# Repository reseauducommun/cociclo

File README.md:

# cociclo
An airborne particles, Carbon Monoxyde (CO), temperature and humidity sensor circuit based on the ESP8266 (Wemos).  One version sends data to mysql and allows for the exploration of visualisations.  The other turns the pollution levels into sound for a participatory walk. 

For more information about the art and activism project : https://artengine.ca/acastonguay

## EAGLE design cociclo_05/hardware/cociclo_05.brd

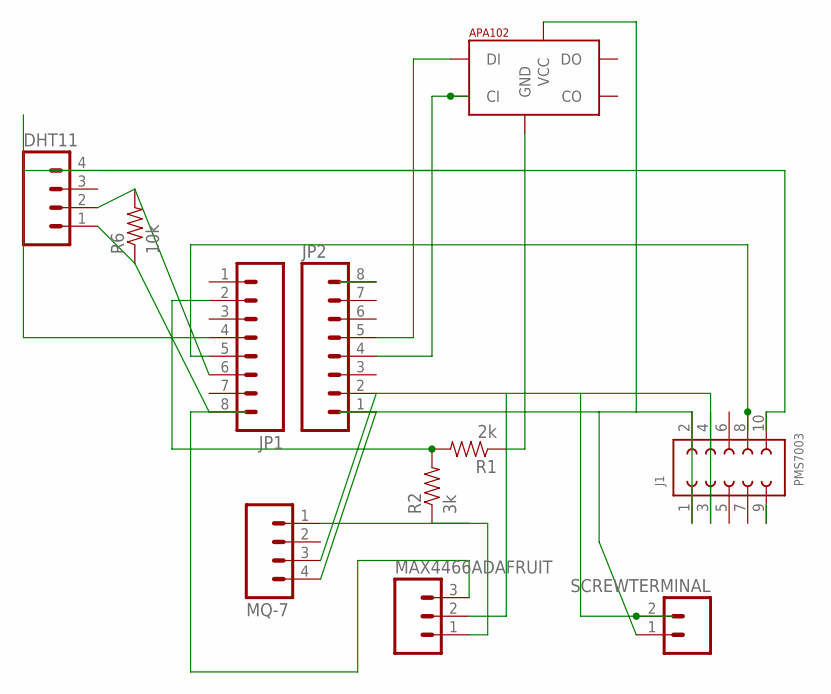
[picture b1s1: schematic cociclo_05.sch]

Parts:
DHT11: M04PTH; 1X04
J1: PMS7003; 621X1021021
JP1, JP2: M08; 1X08_ROUND
MAX4466ADAFRUIT: M03PTH; 1X03
MQ-7: M04PTH; 1X04
R1: 2k; 1206
R2: 3k; 1206
R6: 10k; 1206
SCREWTERMINAL: M023.5MM; SCREWTERMINAL-3.5MM-2
SK9822LED: APA1025050; APA102_5050

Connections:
7RX: J1.8 (7), JP1.5
9TX: J1.10 (6), JP1.4
10SET: J1.9 (5)
+5V: J1.1, J1.2 (10), JP2.1, MQ-7.4, SCREWTERMINAL.1, SK9822LED.1 (VCC)
ADC: JP1.2, R1.2, R2.2
CH_PD: DHT11.1, JP1.8, MAX4466ADAFRUIT.3, R6.1
D2: JP2.5, SK9822LED.4 (DI)
GND: DHT11.4, J1.3 (2), J1.4 (9), JP2.2, MAX4466ADAFRUIT.2, MQ-7.3, R1.1, SCREWTERMINAL.2, SK9822LED.6 (GND)
GPIO14: DHT11.2, JP1.6, R6.2
MQ7ANALOG: MAX4466ADAFRUIT.1, MQ-7.1, R2.1
unnamed: JP2.4, SK9822LED.5 (CI)

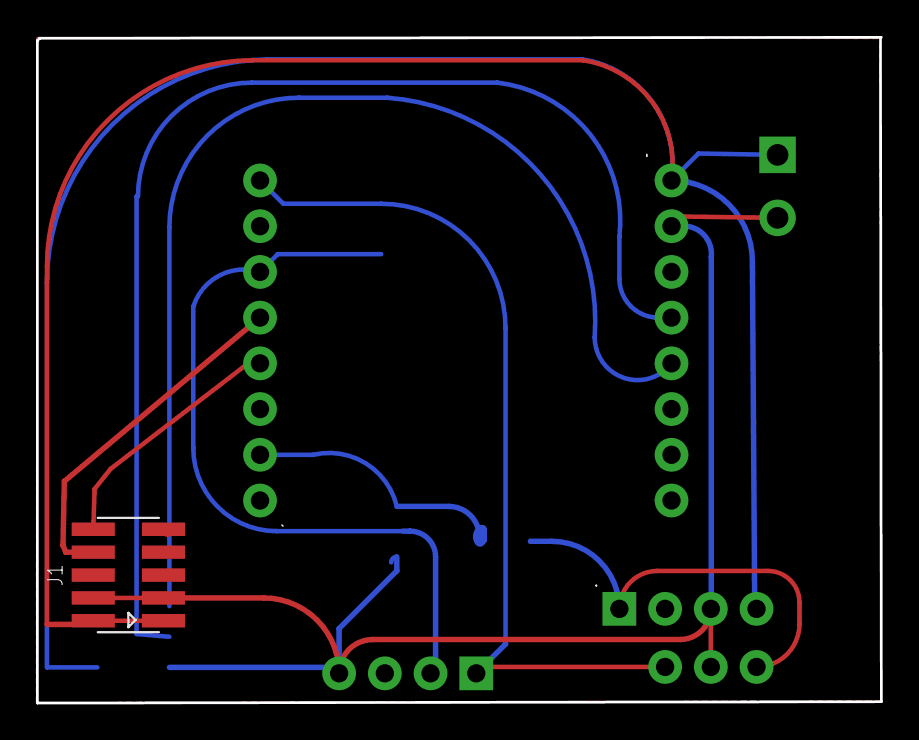
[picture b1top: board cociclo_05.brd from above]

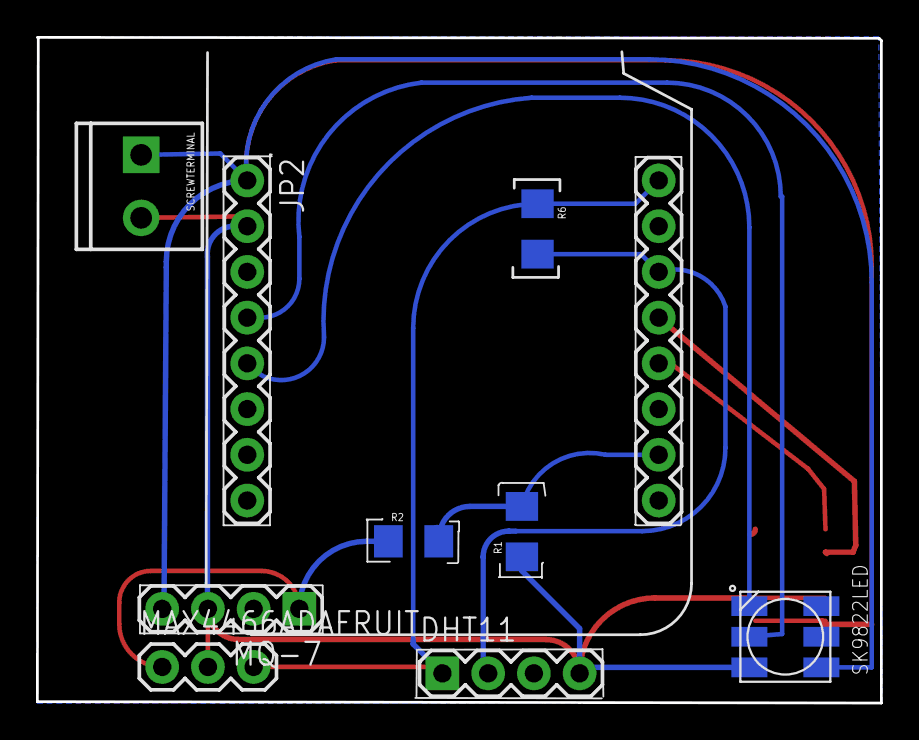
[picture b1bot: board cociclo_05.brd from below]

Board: 2 copper layers, 46.9 x 37.0 mm, 11 parts (10 on the bottom side), 10 nets.

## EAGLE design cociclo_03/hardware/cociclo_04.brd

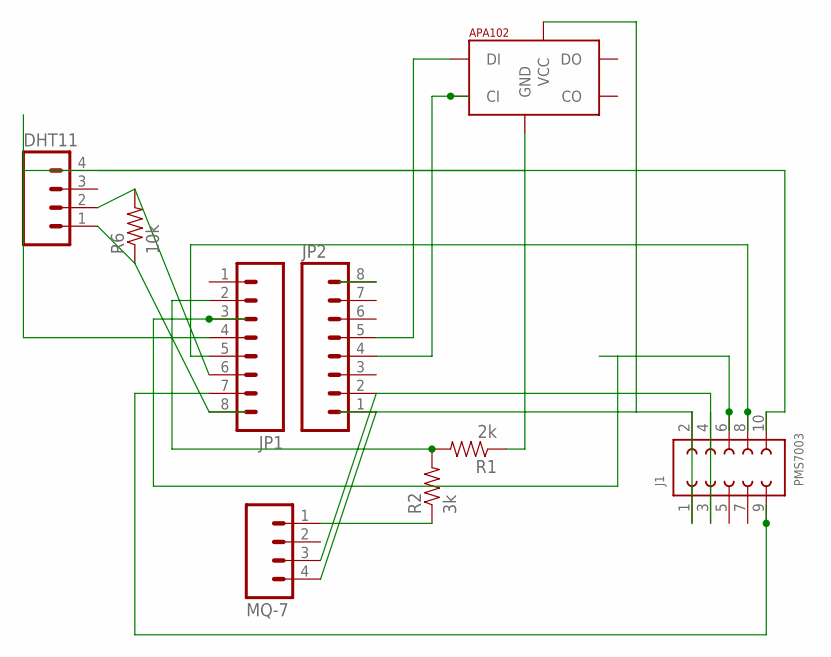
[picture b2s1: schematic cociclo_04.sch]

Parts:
DHT11: M04PTH; 1X04
J1: PMS7003; 621X1021021
JP1, JP2: M08; 1X08_ROUND
LED: APA1025050; APA102_5050
MQ-7: M04PTH; 1X04
R1: 2k; 1206
R2: 3k; 1206
R6: 10k; 1206

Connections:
5RESET: J1.6 (8), JP1.3
7RX: J1.8 (7), JP1.5
9TX: J1.10 (6), JP1.4
10SET: J1.9 (5), JP1.7
+5V: J1.1, J1.2 (10), JP2.1, LED.1 (VCC), MQ-7.4
ADC: JP1.2, R1.2, R2.2
CH_PD: DHT11.1, JP1.8, R6.1
D2: JP2.5, LED.4 (DI)
GND: DHT11.4, J1.3 (2), J1.4 (9), JP2.2, LED.6 (GND), MQ-7.3, R1.1
GPIO14: DHT11.2, JP1.6, R6.2
MQ7ANALOG: MQ-7.1, R2.1
unnamed: JP2.4, LED.5 (CI)

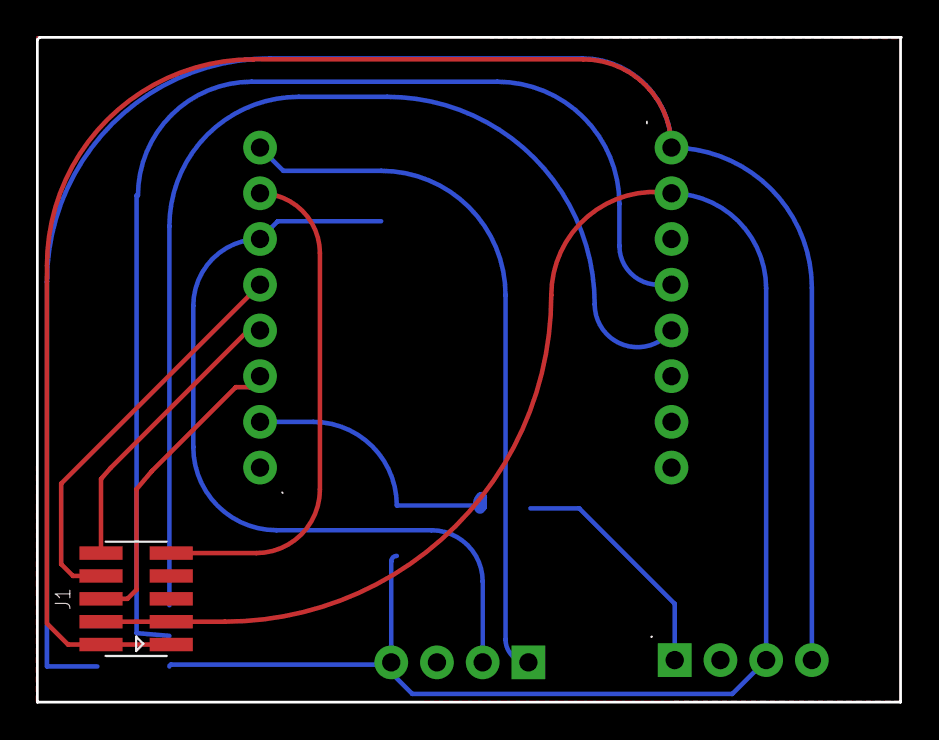
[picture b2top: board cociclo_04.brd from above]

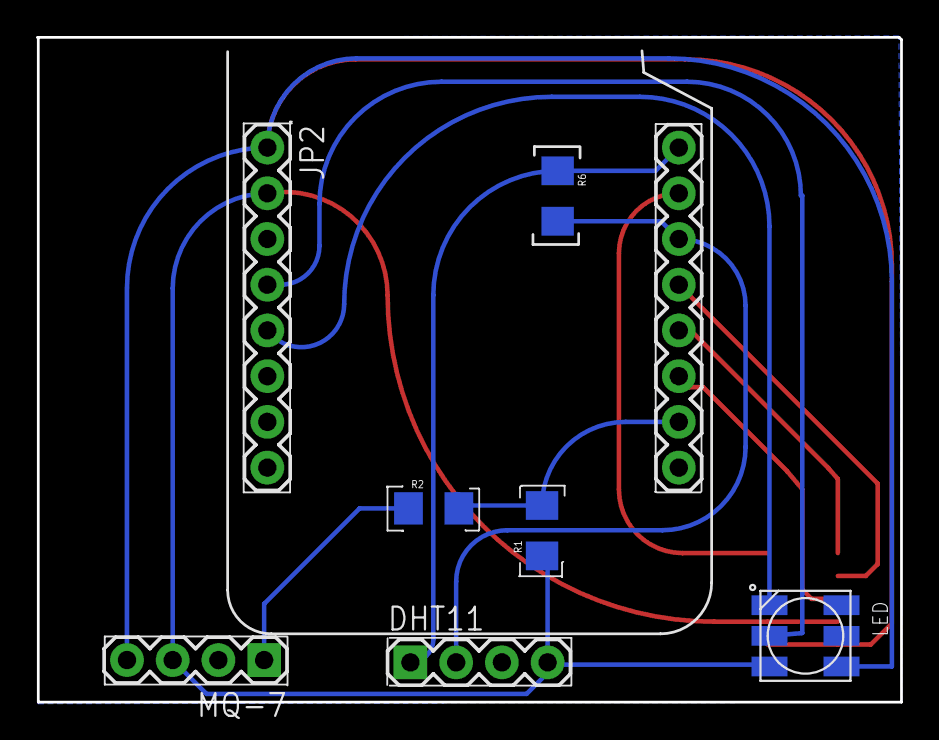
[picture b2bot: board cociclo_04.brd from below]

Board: 2 copper layers, 48.0 x 36.9 mm, 9 parts (8 on the bottom side), 12 nets.

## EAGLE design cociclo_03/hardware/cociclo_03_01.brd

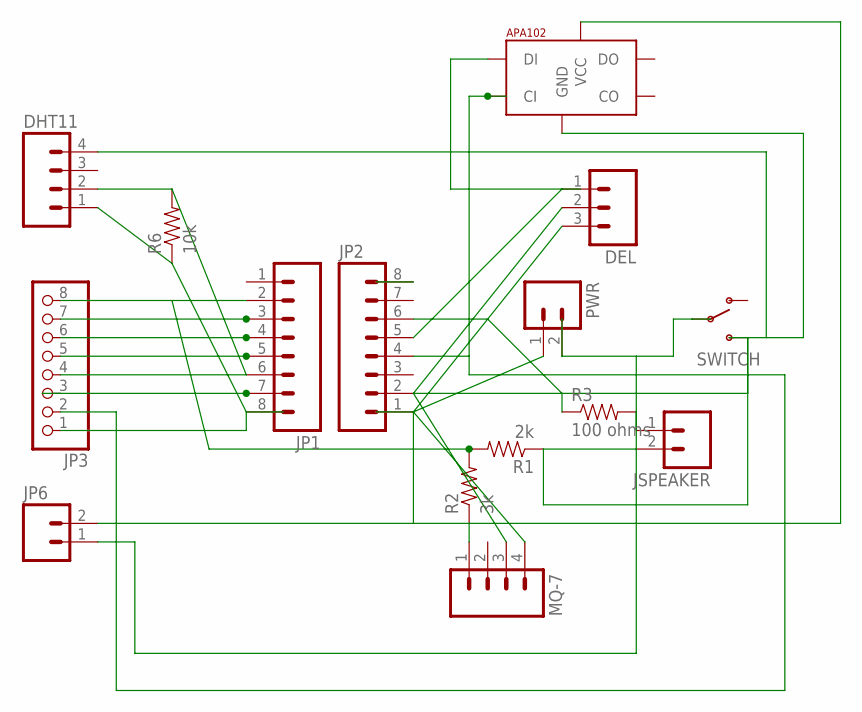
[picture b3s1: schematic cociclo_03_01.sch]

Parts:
DEL: M03PTH; 1X03
DHT11: M04PTH; 1X04
JP1, JP2: M08; 1X08_ROUND
JP3: PINHD-1X8-3.5MM; 1X08-3.5MM
JP6: M023.5MM; SCREWTERMINAL-3.5MM-2
JSPEAKER: M02PTH; 1X02
LED: APA1025050; APA102_5050
MQ-7: M04PTH; 1X04
PWR: M02LOCK_LONGPADS; 1X02_LOCK_LONGPADS
R1: 2k; 1206
R2: 3k; 1206
R3: 100 ohms; 1206
R6: 10k; 1206
SWITCH: SWITCH-SPDTKIT; SWITCH-SPDT_KIT

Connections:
+5V: DEL.3, JP2.1, JP6.2, LED.1 (VCC), MQ-7.4, PWR.1
ADC: JP1.2, JP3.8, R1.2, R2.2
CH_PD: DHT11.1, JP1.8, JP3.1, R6.1
D2: DEL.1, JP2.5, LED.4 (DI)
GND: DEL.2, DHT11.4, JP2.2, JSPEAKER.2, LED.6 (GND), MQ-7.3, R1.1, SWITCH.3 (S)
GPIO12: JP2.6, R3.1
GPIO14: DHT11.2, JP1.6, JP3.4, R6.2
MQ7ANALOG: MQ-7.1, R2.1
unnamed: JSPEAKER.1, R3.2
unnamed: JP1.7, JP3.3
unnamed: JP6.1, PWR.2, SWITCH.2
unnamed: JP2.4, JP3.2, LED.5 (CI)
unnamed: JP1.5, JP3.5
unnamed: JP1.4, JP3.6
unnamed: JP1.3, JP3.7

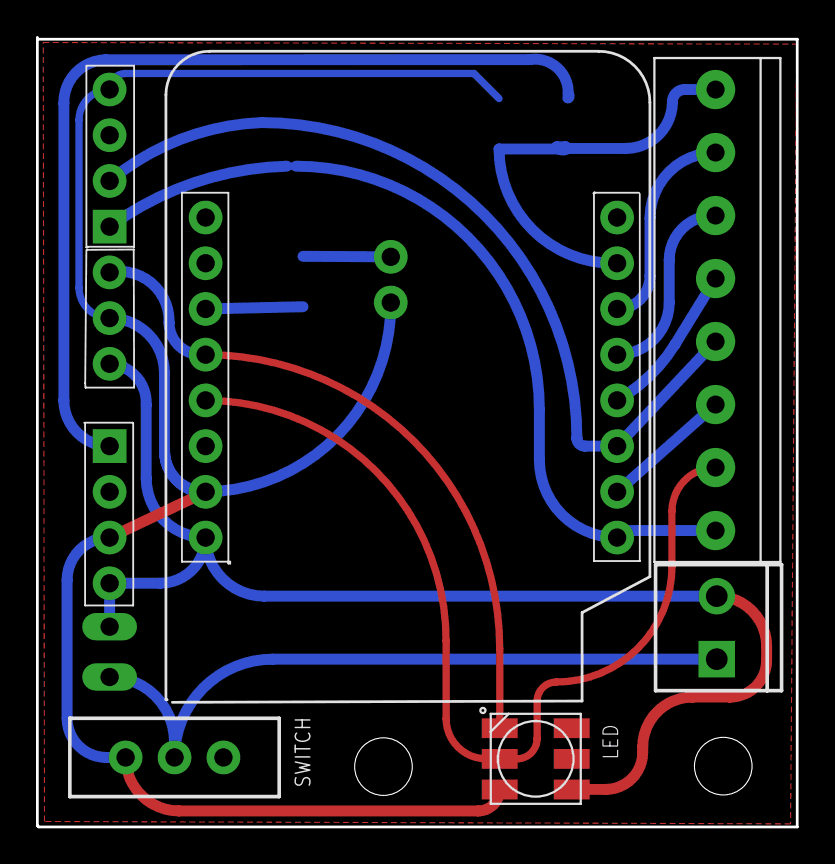
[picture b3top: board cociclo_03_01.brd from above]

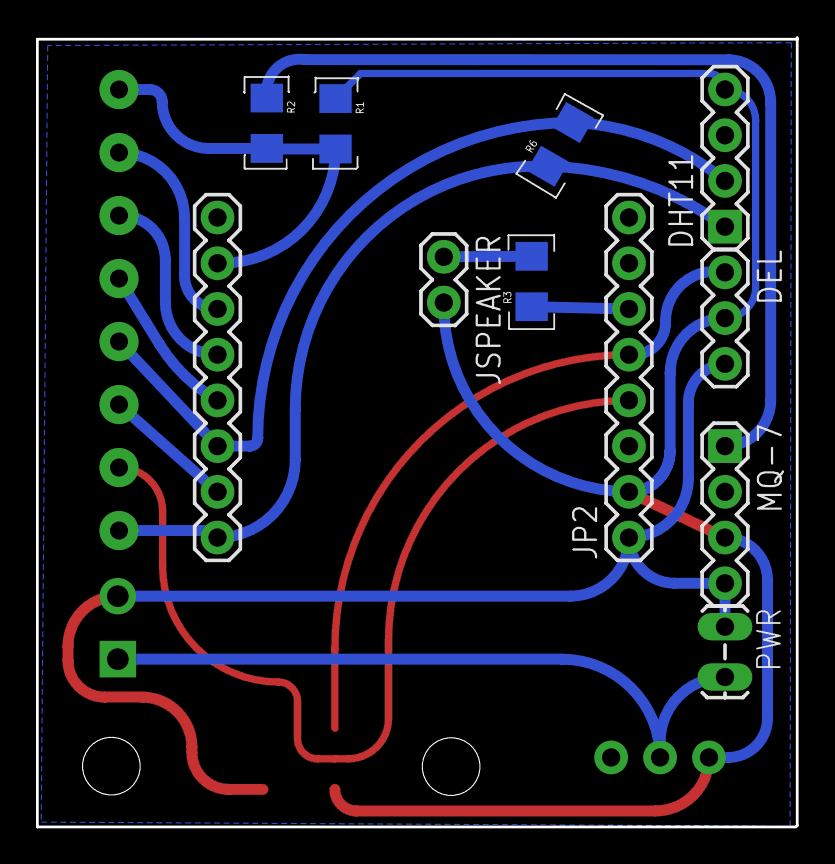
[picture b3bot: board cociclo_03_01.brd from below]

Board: 2 copper layers, 42.2 x 43.9 mm, 15 parts (11 on the bottom side), 15 nets.

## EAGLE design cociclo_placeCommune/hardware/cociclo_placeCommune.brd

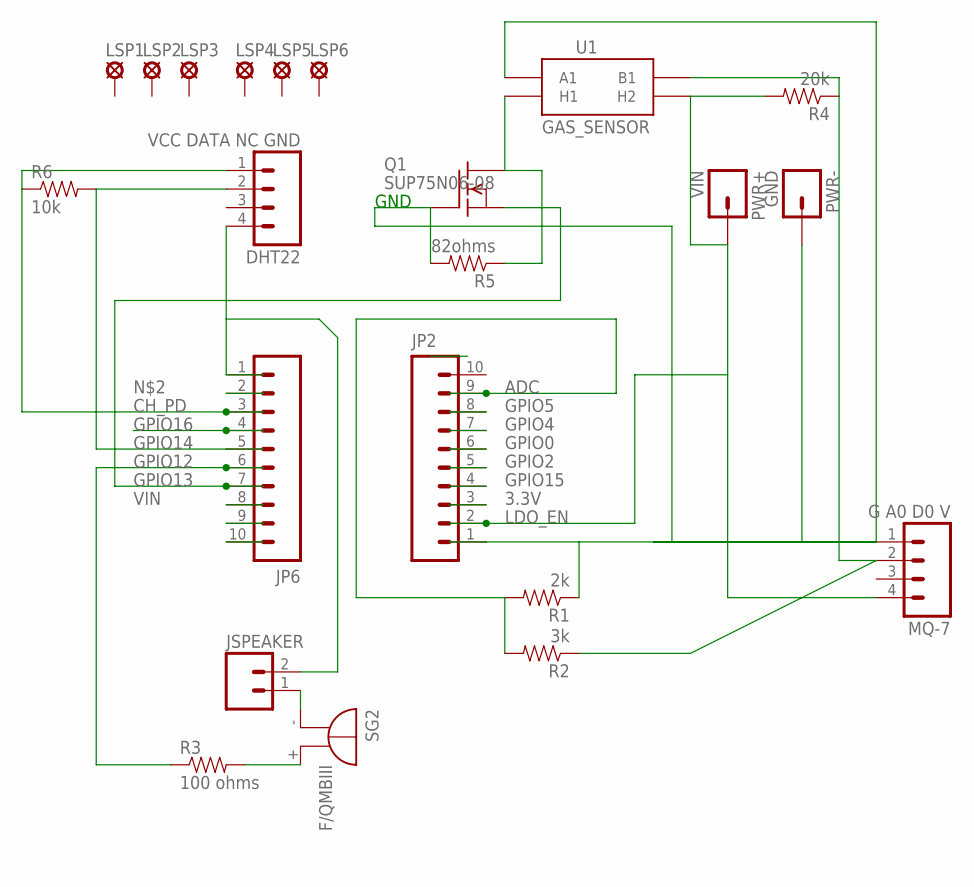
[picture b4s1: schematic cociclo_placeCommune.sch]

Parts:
DHT22: VCC DATA NC GND; 1X04
JP2, JP6: M10SILK_FEMALE_PTH; 1X10
JSPEAKER: M02PTH; 1X02
LSP1, LSP2, LSP3, LSP4, LSP5, LSP6: LSP10
MQ-7: G A0 D0 V; 1X04
PWR+: VIN; 1X01NS-KIT
PWR-: GND; 1X01NS-KIT
Q1: SUP75N06-08; TO220
R1: 2k; 1206
R2: 3k; 1206
R3: 100 ohms; 1206
R4: 20k; 1206
R5: 82ohms; 1206
R6: 10k; 1206
SG2: F/QMBIII
U1: GAS_SENSOR; MQ-3

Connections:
3.3V: JP2.3
ADC: JP2.9, R1.2, R2.2
CH_PD: DHT22.1, JP6.3, R6.1
GND: JP2.1, JP6.10, MQ-7.1, PWR-.1, Q1.1 (G), R1.1, R5.2, U1.A1
GPIO0: JP2.6
GPIO2: JP2.5
GPIO4: JP2.7
GPIO5: JP2.8
GPIO12: JP6.6, R3.1
GPIO13: JP6.7, Q1.3 (S)
GPIO14: DHT22.2, JP6.5, R6.2
GPIO15: JP2.4
GPIO16: JP6.4
LDO_EN: JP2.2, MQ-7.4, PWR+.1, R4.2, U1.HB (H2)
unnamed: MQ-7.2, R2.1, R4.1, U1.B1
unnamed: R3.2, SG2.+ (-)
unnamed: JSPEAKER.1, SG2.- (+)
unnamed: Q1.2 (D), R5.1, U1.HA (H1)
RESET_5V: DHT22.4, JP6.1, JSPEAKER.2
VBAT: JP6.9
VIN: JP6.8

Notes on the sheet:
GND

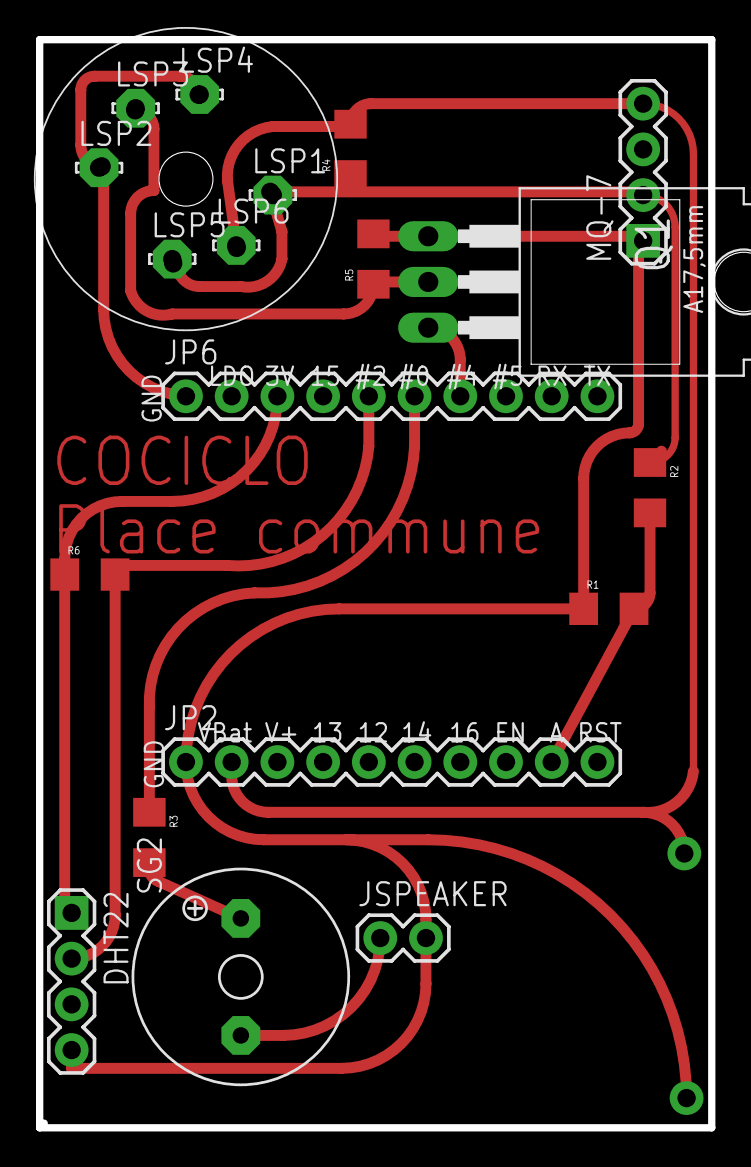
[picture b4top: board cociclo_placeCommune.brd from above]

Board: 2 copper layers, 37.3 x 60.5 mm, 23 parts (1 on the bottom side), 12 nets.

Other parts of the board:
U$2: HUZZAHLOGO

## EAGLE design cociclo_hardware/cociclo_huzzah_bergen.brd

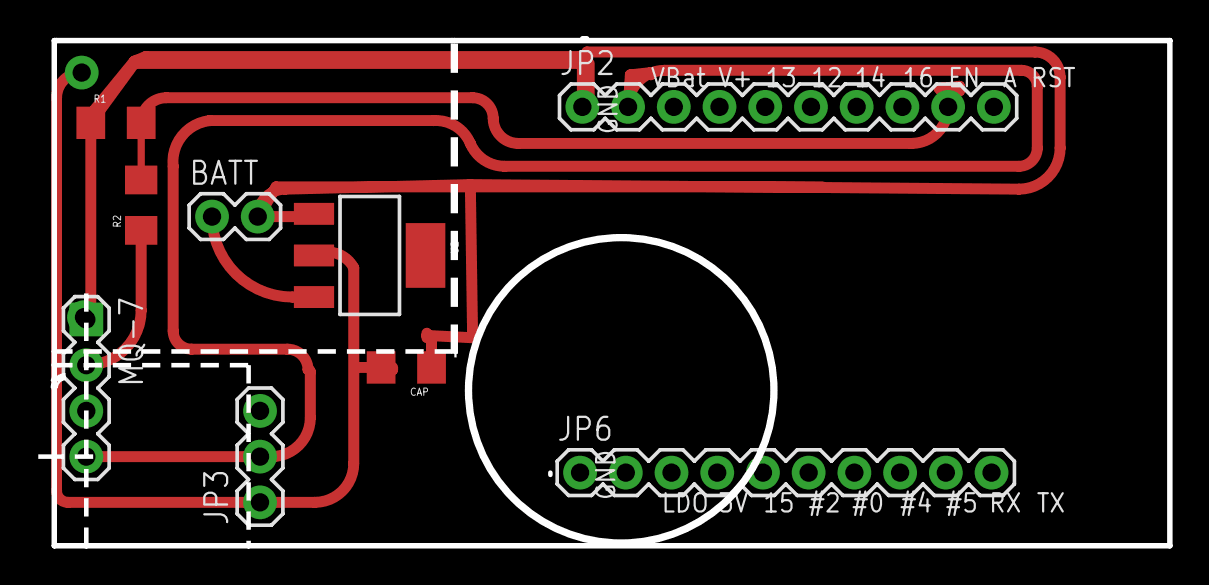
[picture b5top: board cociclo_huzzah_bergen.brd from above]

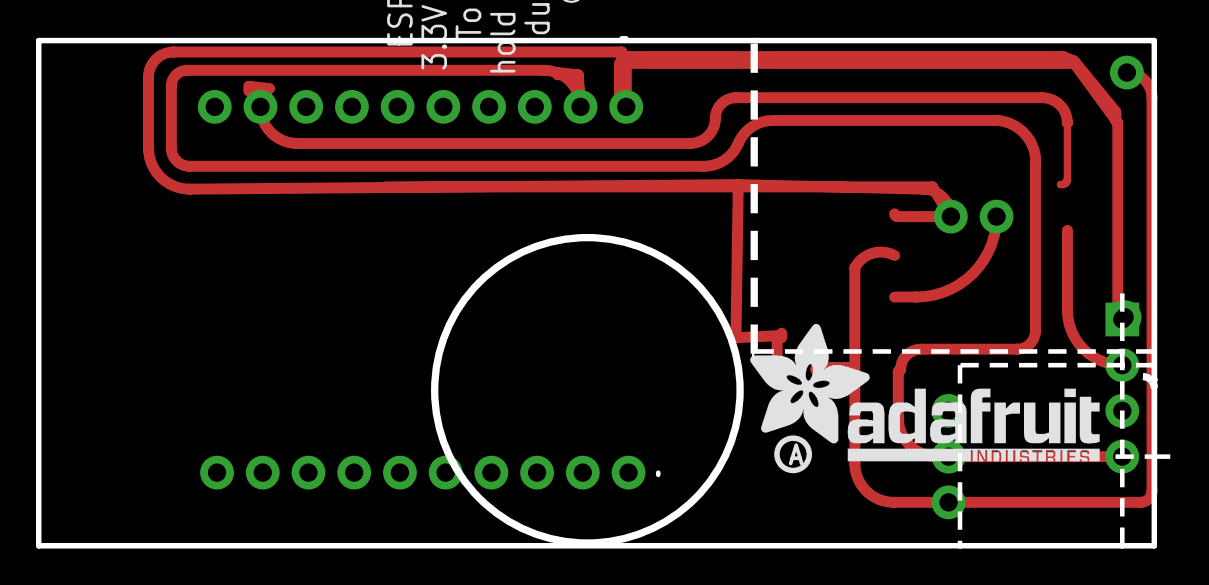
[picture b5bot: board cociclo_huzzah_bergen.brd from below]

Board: 2 copper layers, 62.7 x 28.1 mm, 14 parts (3 on the bottom side), 6 nets.

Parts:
BATT: 1X02
CAP: 470pf; 1206
JP2, JP6: 1X10
JP3: VIN; 1X03
MQ-7: G A0 D0 V; 1X04
PWR+: VIN; 1X01NS-KIT
PWR-: GND; 1X01NS-KIT
R1: 2k; 1206
R2: 3k; 1206
U2: V_REG_317SMD; SOT223
U$2: HUZZAHLOGO
U$12: ADAFRUIT_TEXT_20MM
U$13: PCBFEAT-REV-040

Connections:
ADC: JP2.9, R1.2, R2.2
GND: BATT.2, JP2.1, JP6.10, MQ-7.1, PWR-.1, R1.1, U2.1
LDO_EN: JP2.2, JP3.2, MQ-7.4
unnamed: MQ-7.2, R2.1
unnamed: JP3.1, PWR+.1, U2.2
unnamed: BATT.1, U2.3

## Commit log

2015-06-10 Commit del Noviembre 2014 taller en Cali
    Beta version! Contact me if you would like to build one.
2015-07-20 cordova android project
    This version reads in audio frequencies and displays geolocation
    information. Works for android atm, let me know if you’d like to test
    for iOS.
2015-09-22 Many changes, the hardware part got simpler and the code got more complex.
    The chain from sensor to server functions!
2015-09-23 Explicaciones y el código Arduino
2015-09-23 yo limpio
2015-09-24 archive pour android México et petite correction de commentaire
2015-11-21 Piksel Bergen Version
    Switching to UDP over wifi and a design with the huzzah.
2015-11-21 no alert
2015-11-21 build
2015-12-14 petit changement pour la version de Bergen
2015-12-14 Huzzah version
    Version de Arles, fonctionne avec le esp8266.
2016-04-01 Cociclo PlaceCommune
    Tout le nécessaire pour la version 'base' du Cociclo.
2016-04-01 Ajout du coût des plaquettes et DHT
    Le coût réel des plaquettes et des capteurs de température + humidité
2016-04-02 Infos sur les composantes
    Ajout des valeurs des résistances et des connexions.
2016-04-02 Sensors
    Les capteurs MQ7 (monoxyde de carbone) et DHT11 (Température et humidité) (équivalent au DHT22)
2016-04-02 MQ7
    Avec les valeurs de ses broches.
2016-04-02 MQ7 de sainsmart
    ...la bonne version!
2016-04-05 sélection des utilisateurs depuis la bd
    + Ajout d'un menu pour la sélection des utilisateurs lors de la sélection des données. CO.php fait un appel à la base de données via un argument d'URL à conversion.php
    + Un peu de ménage avec un .css
    + Des essais de logos
    = doit ajouter un champ pour l'adresse MAC du esp8266 afin de distinguer les utilisateurs
    = doit modifier le code Arduino pour le recueillir et aussi proposer un
    = doit réduire la fréquence d'envois (passer de 7 secondes à un par minute) à la base de données et prévoir une moyenne glissante
2016-04-20 Update connect2.php
    Est-ce qu'il serait possible de faire une vérification sur la 'MAC address' de chaque cociclo? Parce que c'est maintenant la première donnée envoyée. Ça serait super sécur? Les types des données sont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
2016-04-20 Update cociclo_placeCommune.ino
    Ajout de la 'MAC address', de la moyenne et des valeurs maximales. Pour augmenter le délai entre les écritures dans la base de données, simplement augmentez la valeur de la variable 'lecture'.
    Added polling for the MAC Address, a means and a maximum for the CO readings. Increase the value of 'lectures' in order to augment the delay between writes to the database.
    Merci Wassim!
2016-05-03 Howto solder the board
2016-05-03 How to configure your cocíclo
2016-08-16 versión para wemos, estación y portable
2016-08-29 Update connect2.php
    mise à jour de la structure de la base de donnée par création d'une table par utilisateur
2016-09-01 3D models for the base station
2016-09-01 Infos sobre el taller
2016-09-01 gcode para una DittoPRO (1,75mm filament)
2016-09-07 official version!
2016-09-08 Howto configure your access point (english version)
2016-09-08 hacemos ruidos!!
2016-09-08 para la calibración
2016-09-26 updated description
2016-10-08 Delay value set to 20 minutes for the sensor burn-in
2018-01-28 old code + files
2018-01-28 Descripción taller transpiksel MX
2018-01-28 version 03
    + Plantones PMS3003 gracias unloquer
    + Dotstar SK9822 RGB LED
2018-01-28 cociclo v3 BOM
2018-01-29 PMS3003 works!
    Next step is to integrate everything in the main code
2018-10-10 From december 2017!
    TODO : add the Plantower sensor, automatic geolocation
2018-10-10 début de la version 05 et fichiers grb
2018-10-15 intégration du PMS300 refactorisation du code
    peut maintenant détecter la pollution par les particules
    auto détecte la localisation
2018-10-15 nouvelle structure
2018-10-19 listos!
    intégration de la routine de géolocalisation
    de l’indication avec la DEL dotstar
    et avec le script PHP d’écriture dans la base de données
2018-11-08 hasta la 1.0 :)
    Adición logo unloquer
    Adición opción para Adafruit MAX 4466
    Adición ‘screw terminal’
2019-02-26 commit
    a typeDonnees field to distinguish the type of data collected
2019-05-31 oui entrée audio!
    Tout simple, reste *seulement* à calibrer ;).
2019-05-31 ben oui
    heh
2019-05-31 nettoyage
    oui
2019-06-05 test pour les DEls dotstar
    ouin
2024-06-07 Update cociclo_marqueur.ino
    Reference to the Dioxygraphe d'Andrew Chartier -> https://esse.ca/portfolio/andrew-chartier/

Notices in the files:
parts and their libraries:
SparkFun-Connectors: Licensing: Creative Commons ShareAlike 4.0 International - https://creativecommons.org/licenses/by-sa/4.0
Board-to-Board: Copyright: Würth Elektronik
